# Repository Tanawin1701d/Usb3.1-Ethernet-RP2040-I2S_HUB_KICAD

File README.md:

# Usb3.1-Ethernet-RP2040-I2S_HUB_KICAD

- This project relies on Kicad 9.0

## features

### input
- usb 3.1 gen2
### output
- usb 3.0 (2 ports)
- ethernet (1 rj45 port)
- microphone + speaker (stero 3mm jack)
### processor & ic
- Rasberry pi (RP2040)
- tmp235 (temperature sensor)
- tusb8041 (usb hub)
- RTL8153B-VB (ethernet)

### repo structure

```
F---- doc (document for each ICs)
F---- finalProj
           |F---- hub (kicad file)
F---- symFoot (footprint for each ICs)
D---- bom.xlsx (bill of material for all components except pcb board)
```

## preview

### schematic

### layout

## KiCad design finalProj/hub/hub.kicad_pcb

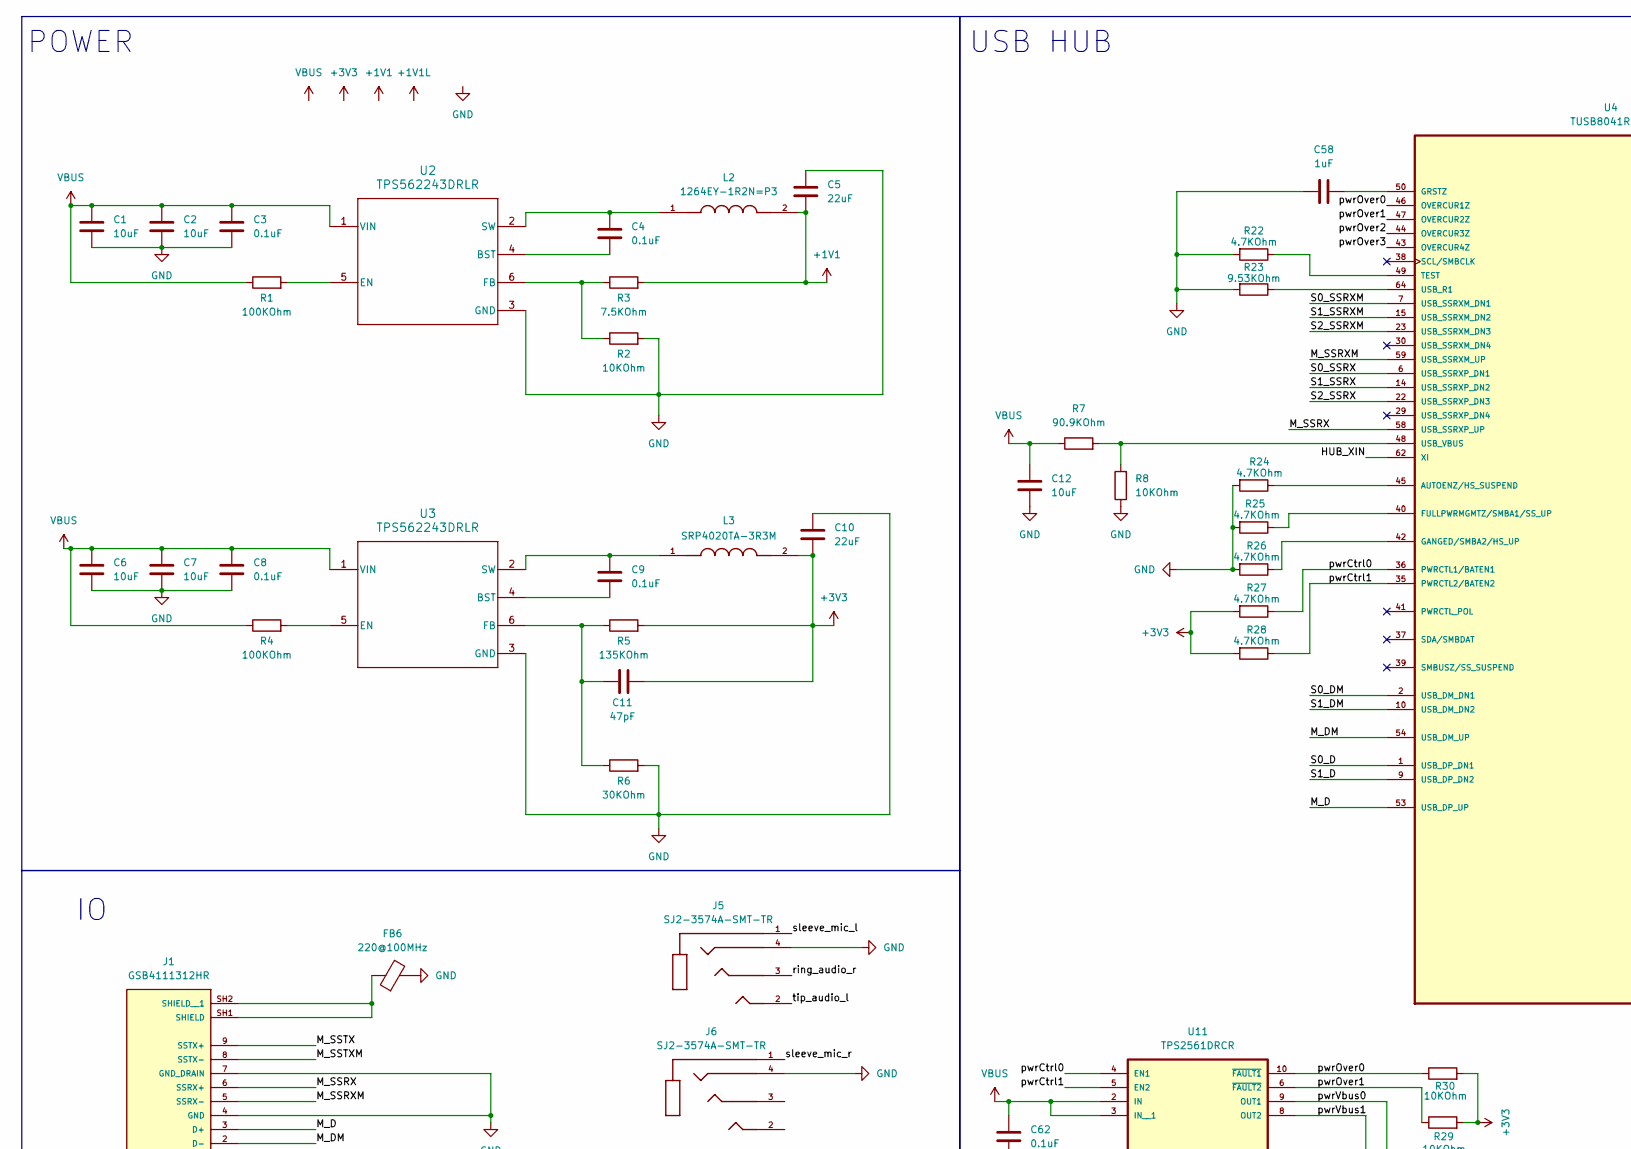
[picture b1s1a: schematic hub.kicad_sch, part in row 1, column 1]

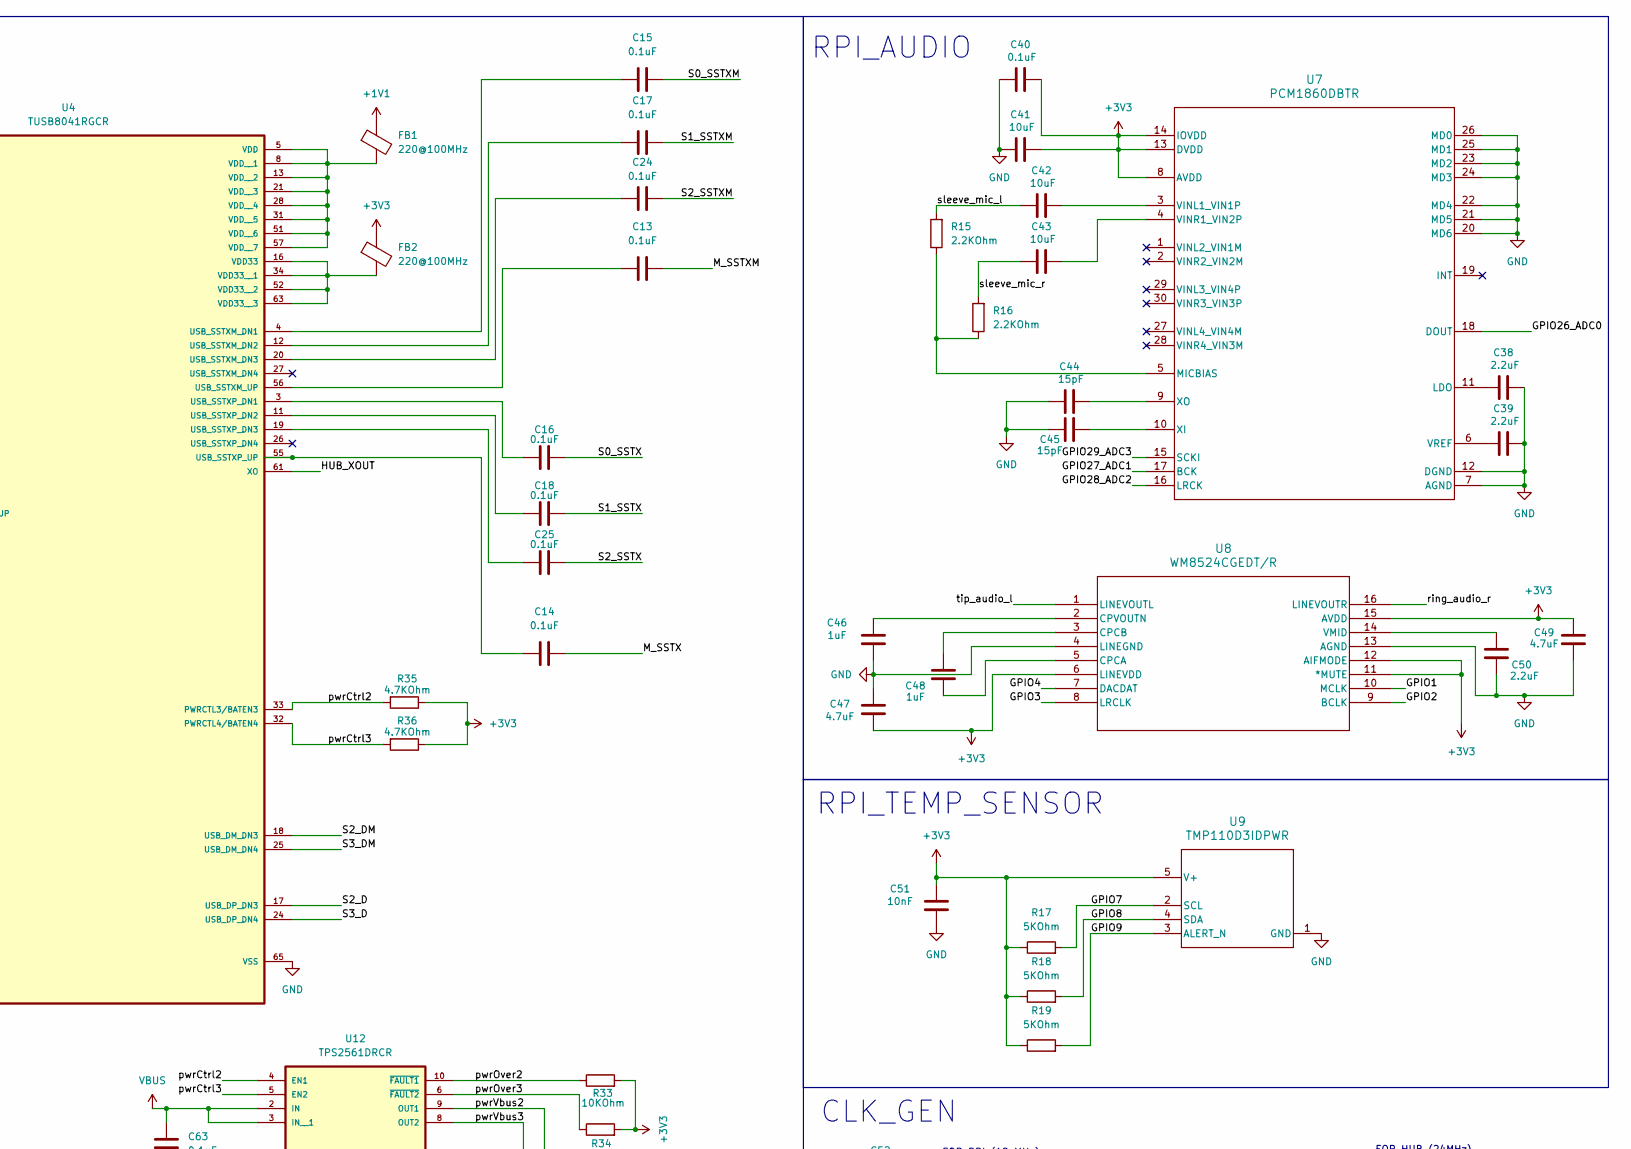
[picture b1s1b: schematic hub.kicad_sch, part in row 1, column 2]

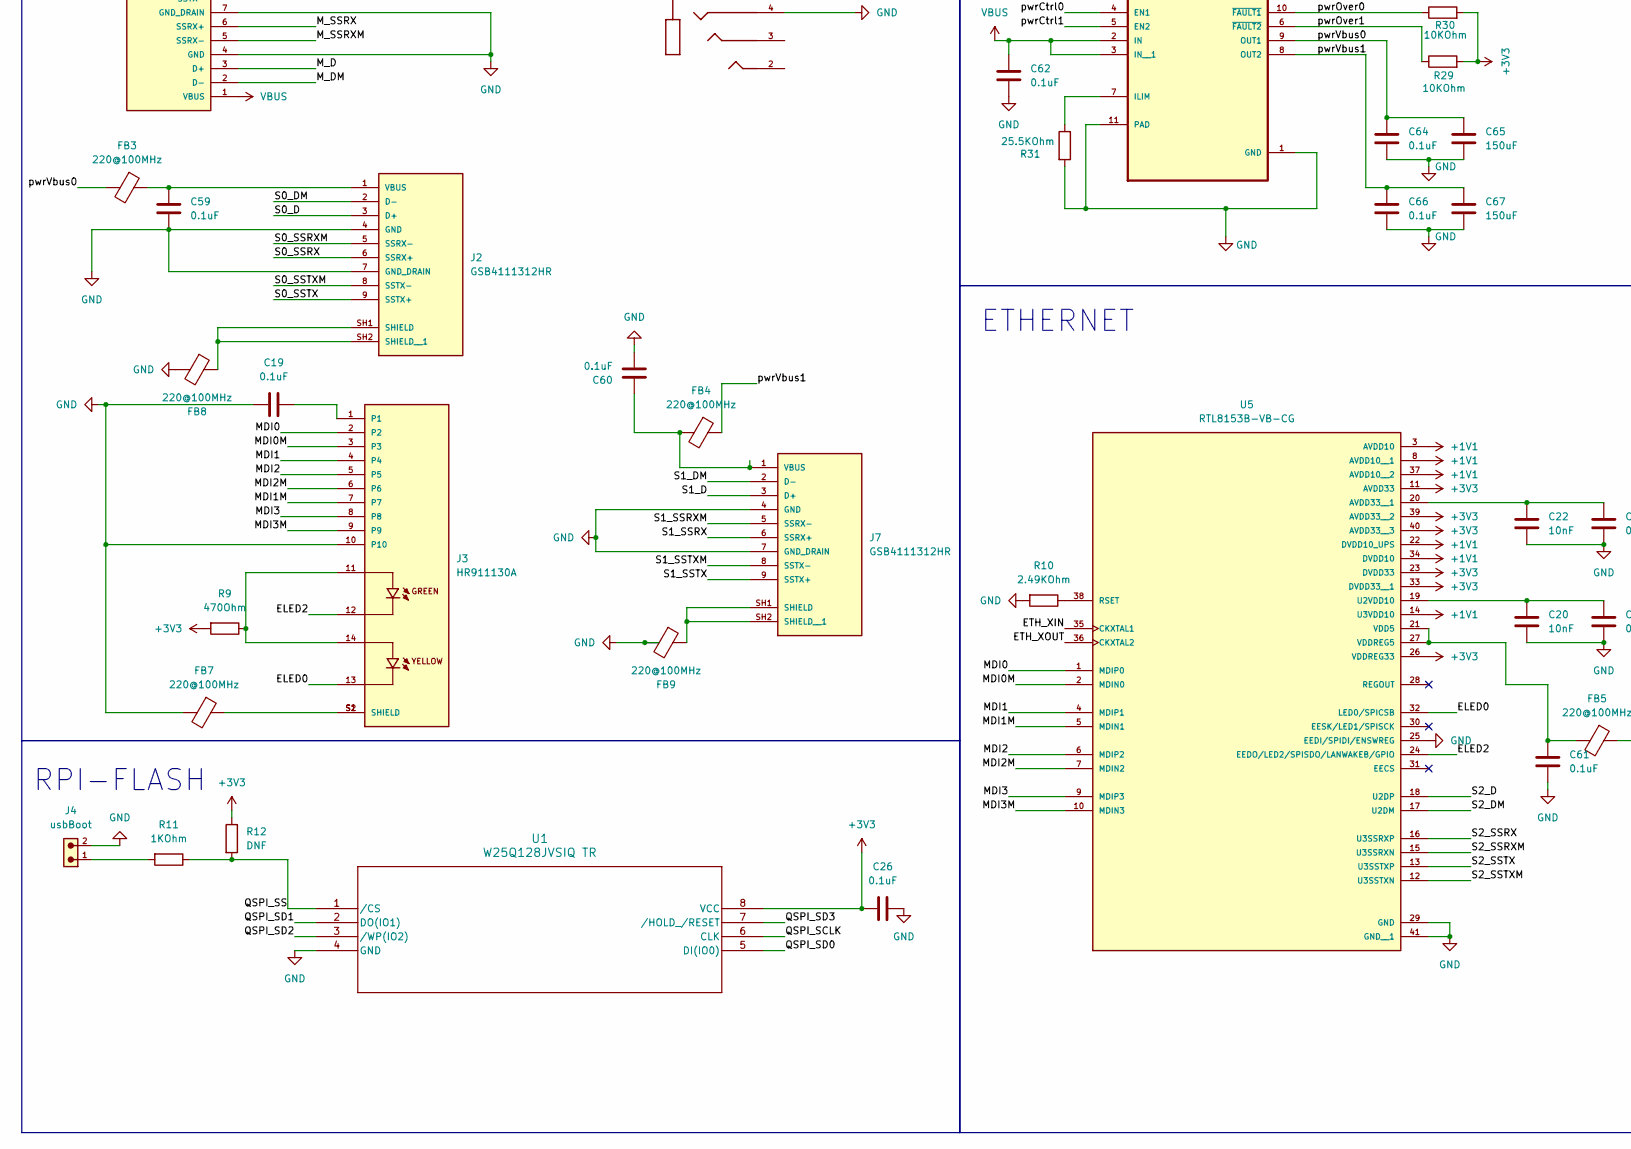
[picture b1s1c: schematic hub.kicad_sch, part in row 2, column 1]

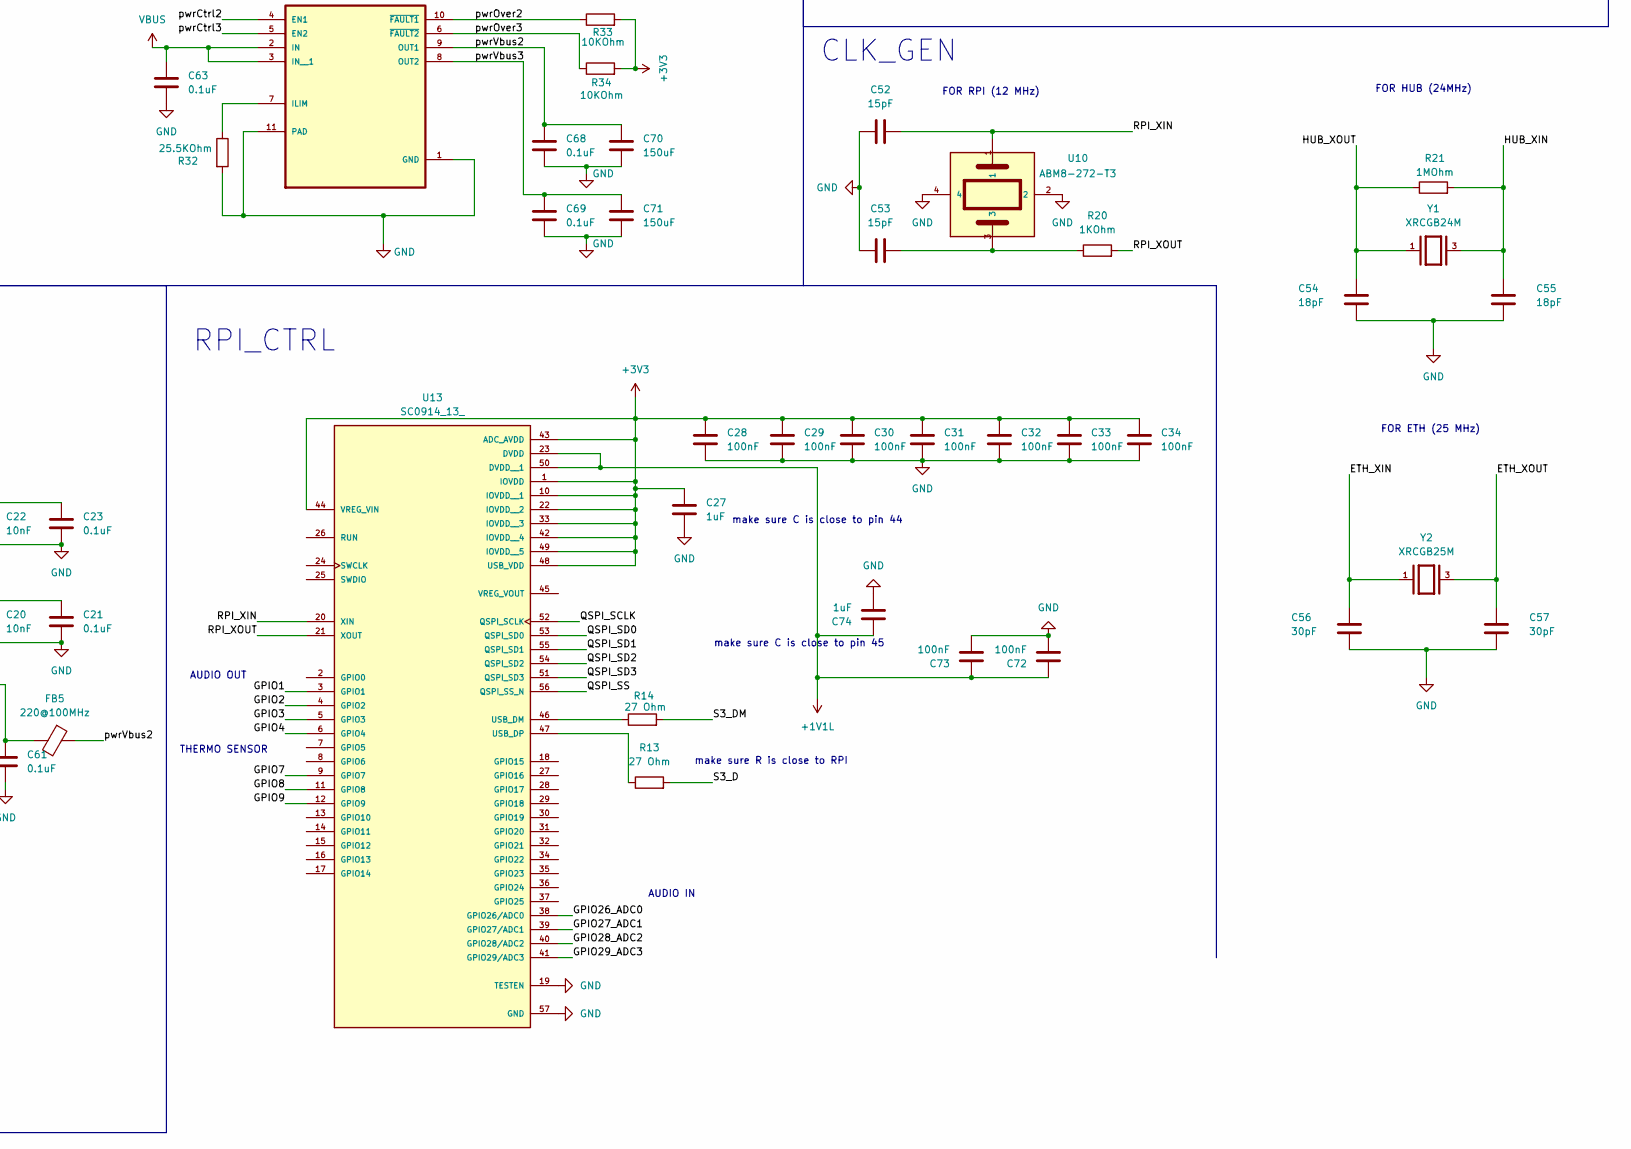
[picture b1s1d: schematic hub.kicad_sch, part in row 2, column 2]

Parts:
C1, C2, C6, C7, C12, C41, C42, C43: 10uF; C_0805_2012Metric_Pad1.18x1.45mm_HandSolder
C3, C4, C8, C9, C13, C14, C15, C16, C17, C18, C19, C21, C23, C24, C25, C26, C40, C59, C60, C61, C62, C63, C64, C66, C68, C69: 0.1uF; C_0603_1608Metric_Pad1.08x0.95mm_HandSolder
C5, C10: 22uF; C_1206_3216Metric_Pad1.33x1.80mm_HandSolder
C11: 47pF; C_0603_1608Metric_Pad1.08x0.95mm_HandSolder
C20, C22, C51: 10nF; C_0603_1608Metric_Pad1.08x0.95mm_HandSolder
C27, C46, C48, C58, C74: 1uF; C_0603_1608Metric_Pad1.08x0.95mm_HandSolder
C28, C29, C30, C31, C32, C33, C34, C72, C73: 100nF; C_0603_1608Metric_Pad1.08x0.95mm_HandSolder
C38, C39, C50: 2.2uF; C_0603_1608Metric_Pad1.08x0.95mm_HandSolder
C44, C45, C52, C53: 15pF; C_0805_2012Metric_Pad1.18x1.45mm_HandSolder
C47, C49: 4.7uF; C_0805_2012Metric_Pad1.18x1.45mm_HandSolder
C54, C55: 18pF; C_0603_1608Metric_Pad1.08x0.95mm_HandSolder
C56, C57: 30pF; C_0805_2012Metric_Pad1.18x1.45mm_HandSolder
C65, C67, C70, C71: 150uF; CP_Radial_D6.3mm_P2.50mm
FB1, FB2, FB3, FB4, FB5, FB6, FB7, FB8, FB9: 220@100MHz; L_0603_1608Metric_Pad1.05x0.95mm_HandSolder
J1, J2, J7: GSB4111312HR; AMPHENOL_GSB4111312HR; PARTREV B
J3: HR911130A; HANRUN_HR911130A; PARTREV A
J4: usbBoot; 61300211121
J5, J6: SJ2-3574A-SMT-TR; SAMESKY_SJ2-3574A-SMT-TR; PARTREV 1.05
L2: 1264EY-1R2N=P3; IND_1264EY-1R2N=P3; PARTREV N/A
L3: SRP4020TA-3R3M; IND_SRP4020TA-3R3M
R1, R4: 100KOhm; R_0603_1608Metric_Pad0.98x0.95mm_HandSolder
R2, R8, R29, R30, R33, R34: 10KOhm; R_0603_1608Metric_Pad0.98x0.95mm_HandSolder
R3: 7.5KOhm; R_0603_1608Metric_Pad0.98x0.95mm_HandSolder
R5: 135KOhm; R_0603_1608Metric_Pad0.98x0.95mm_HandSolder
R6: 30KOhm; R_0603_1608Metric_Pad0.98x0.95mm_HandSolder
R7: 90.9KOhm; R_0603_1608Metric_Pad0.98x0.95mm_HandSolder
R9: 470Ohm; R_0603_1608Metric_Pad0.98x0.95mm_HandSolder
R10: 2.49KOhm; R_0603_1608Metric_Pad0.98x0.95mm_HandSolder
R11, R20: 1KOhm; R_0603_1608Metric_Pad0.98x0.95mm_HandSolder
R12: DNF; R_0603_1608Metric_Pad0.98x0.95mm_HandSolder
R13, R14: 27 Ohm; R_0603_1608Metric_Pad0.98x0.95mm_HandSolder
R15, R16: 2.2KOhm; R_0603_1608Metric_Pad0.98x0.95mm_HandSolder
R17, R18, R19: 5KOhm; R_0603_1608Metric_Pad0.98x0.95mm_HandSolder
R21: 1MOhm; R_0603_1608Metric_Pad0.98x0.95mm_HandSolder
R22, R24, R25, R26, R27, R28, R35, R36: 4.7KOhm; R_0603_1608Metric_Pad0.98x0.95mm_HandSolder
R23: 9.53KOhm; R_0603_1608Metric_Pad0.98x0.95mm_HandSolder
R31, R32: 25.5KOhm; R_0603_1608Metric_Pad0.98x0.95mm_HandSolder
U1: W25Q128JVSIQ TR; SOIC_208MIL_WIN
U2, U3: TPS562243DRLR; DRL0006A-MFG
U4: TUSB8041RGCR; QFN50P900X900X100-65N
U5: RTL8153B-VB-CG; QFN40P500X500X90-41N; PARTREV 1.4
U7: PCM1860DBTR; DBT0030A_N
U8: WM8524CGEDT/R; TSSOP16_DM013.B_CIR
U9: TMP110D3IDPWR; DPW0005A-MFG
U10: ABM8-272-T3
U11, U12: TPS2561DRCR; VREG_V62_16624-01YE
U13: SC0914_13_; QFN40P700X700X90-57N; PARTREV 2.2
Y1: XRCGB24M; OSC_XRCGB24M000F2P00R0; PARTREV N/A
Y2: XRCGB25M; OSC_XRCGB25M000F3M00R0; PARTREV N/A

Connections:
+1V1: C5.1, FB1.1, L2.2, R3.2, U5.3 (AVDD10), U5.8 (AVDD10__1), U5.14 (U3VDD10), U5.22 (DVDD10_UPS), U5.34 (DVDD10), U5.37 (AVDD10__2)
+3V3: C10.1, C11.1, C26.1, C27.1, C28.1, C29.1, C30.1, C31.1, C32.1, C33.1, C34.1, C40.2, C41.2, C47.1, C49.2, C51.2, FB2.1, L3.2, R5.2, R9.2, R12.1, R17.1, R18.1, R19.1, R27.2, R28.2, R29.2, R30.2, R33.2, R34.2, R35.1, R36.1, U1.8 (VCC), U5.11 (AVDD33), U5.23 (DVDD33), U5.26 (VDDREG33), U5.33 (DVDD33__1), U5.39 (AVDD33__2), U5.40 (AVDD33__3), U7.8 (AVDD), U7.13 (DVDD), U7.14 (IOVDD), U8.6 (LINEVDD), U8.11 (*MUTE), U8.12 (AIFMODE), U8.15 (AVDD), U9.5 (V+), U13.1 (IOVDD), U13.10 (IOVDD__1), U13.22 (IOVDD__2), U13.33 (IOVDD__3), U13.42 (IOVDD__4), U13.43 (ADC_AVDD), U13.44 (VREG_VIN), U13.48 (USB_VDD), U13.49 (IOVDD__5)
/ELED0: J3.13, U5.32 (LED0/SPICSB)
/ELED2: J3.12, U5.24 (EEDO/LED2/SPISDO/LANWAKEB/GPIO)
/ETH_XIN: C56.1, U5.35 (CKXTAL1), Y2.1
/ETH_XOUT: C57.1, U5.36 (CKXTAL2), Y2.3
/GPIO1: U8.10 (MCLK), U13.3 (GPIO1)
/GPIO2: U8.9 (BCLK), U13.4 (GPIO2)
/GPIO3: U8.8 (LRCLK), U13.5 (GPIO3)
/GPIO4: U8.7 (DACDAT), U13.6 (GPIO4)
/GPIO7: R17.2, U9.2 (SCL), U13.9 (GPIO7)
/GPIO8: R18.2, U9.4 (SDA), U13.11 (GPIO8)
/GPIO9: R19.2, U9.3 (ALERT_N), U13.12 (GPIO9)
/GPIO26_ADC0: U7.18 (DOUT), U13.38 (GPIO26/ADC0)
/GPIO27_ADC1: U7.17 (BCK), U13.39 (GPIO27/ADC1)
/GPIO28_ADC2: U7.16 (LRCK), U13.40 (GPIO28/ADC2)
/GPIO29_ADC3: U7.15 (SCKI), U13.41 (GPIO29/ADC3)
/HUB_XIN: C55.1, R21.2, U4.62 (XI), Y1.3
/HUB_XOUT: C54.1, R21.1, U4.61 (XO), Y1.1
/MDI0: J3.2, U5.1 (MDIP0)
/MDI0M: J3.3, U5.2 (MDIN0)
/MDI1: J3.4, U5.4 (MDIP1)
/MDI1M: J3.7, U5.5 (MDIN1)
/MDI2: J3.5, U5.6 (MDIP2)
/MDI2M: J3.6, U5.7 (MDIN2)
/MDI3: J3.8, U5.9 (MDIP3)
/MDI3M: J3.9, U5.10 (MDIN3)
/M_D: J1.3 (D+), U4.53 (USB_DP_UP)
/M_DM: J1.2 (D-), U4.54 (USB_DM_UP)
/M_SSRX: J1.6 (SSRX+), U4.58 (USB_SSRXP_UP)
/M_SSRXM: J1.5 (SSRX-), U4.59 (USB_SSRXM_UP)
/M_SSTX: C14.2, J1.9 (SSTX+)
/M_SSTXM: C13.2, J1.8 (SSTX-)
/QSPI_SCLK: U1.6 (CLK), U13.52 (QSPI_SCLK)
/QSPI_SD0: U1.5 (DI(IO0)), U13.53 (QSPI_SD0)
/QSPI_SD1: U1.2 (DO(IO1)), U13.55 (QSPI_SD1)
/QSPI_SD2: U1.3 (/WP(IO2)), U13.54 (QSPI_SD2)
/QSPI_SD3: U1.7 (/HOLD_/RESET), U13.51 (QSPI_SD3)
/QSPI_SS: R11.1, R12.2, U1.1 (/CS), U13.56 (QSPI_SS_N)
/RPI_XIN: C52.1, U10.1, U13.20 (XIN)
/RPI_XOUT: R20.2, U13.21 (XOUT)
/S0_D: J2.3 (D+), U4.1 (USB_DP_DN1)
/S0_DM: J2.2 (D-), U4.2 (USB_DM_DN1)
/S0_SSRX: J2.6 (SSRX+), U4.6 (USB_SSRXP_DN1)
/S0_SSRXM: J2.5 (SSRX-), U4.7 (USB_SSRXM_DN1)
/S0_SSTX: C16.2, J2.9 (SSTX+)
/S0_SSTXM: C15.2, J2.8 (SSTX-)
/S1_D: J7.3 (D+), U4.9 (USB_DP_DN2)
/S1_DM: J7.2 (D-), U4.10 (USB_DM_DN2)
/S1_SSRX: J7.6 (SSRX+), U4.14 (USB_SSRXP_DN2)
/S1_SSRXM: J7.5 (SSRX-), U4.15 (USB_SSRXM_DN2)
/S1_SSTX: C18.2, J7.9 (SSTX+)
/S1_SSTXM: C17.2, J7.8 (SSTX-)
/S2_D: U4.17 (USB_DP_DN3), U5.18 (U2DP)
/S2_DM: U4.18 (USB_DM_DN3), U5.17 (U2DM)
/S2_SSRX: U4.22 (USB_SSRXP_DN3), U5.16 (U3SSRXP)
/S2_SSRXM: U4.23 (USB_SSRXM_DN3), U5.15 (U3SSRXN)
/S2_SSTX: C25.2, U5.13 (U3SSTXP)
/S2_SSTXM: C24.2, U5.12 (U3SSTXN)
/S3_D: R13.2, U4.24 (USB_DP_DN4)
/S3_DM: R14.2, U4.25 (USB_DM_DN4)
/pwrCtrl0: R27.1, U4.36 (PWRCTL1/BATEN1), U11.4 (EN1)
/pwrCtrl1: R28.1, U4.35 (PWRCTL2/BATEN2), U11.5 (EN2)
/pwrCtrl2: R35.2, U4.33 (PWRCTL3/BATEN3), U12.4 (EN1)
/pwrCtrl3: R36.2, U4.32 (PWRCTL4/BATEN4), U12.5 (EN2)
/pwrOver0: R30.1, U4.46 (OVERCUR1Z), U11.10 (~FAULT1)
/pwrOver1: R29.1, U4.47 (OVERCUR2Z), U11.6 (~FAULT2)
/pwrOver2: R33.1, U4.44 (OVERCUR3Z), U12.10 (~FAULT1)
/pwrOver3: R34.1, U4.43 (OVERCUR4Z), U12.6 (~FAULT2)
/pwrVbus0: C64.2, C65.2, FB3.2, U11.9 (OUT1)
/pwrVbus1: C66.2, C67.2, FB4.1, U11.8 (OUT2)
/pwrVbus2: C68.2, C70.2, FB5.1, U12.9 (OUT1)
/pwrVbus3: C69.2, C71.2, U12.8 (OUT2)
/ring_audio_r: J5.3, U8.16 (LINEVOUTR)
/sleeve_mic_l: C42.1, J5.1, R15.2
/sleeve_mic_r: C43.1, J6.1, R16.2
/tip_audio_l: J5.2, U8.1 (LINEVOUTL)
GND: C1.1, C2.1, C3.1, C5.2, C6.1, C7.1, C8.1, C10.2, C12.1, C19.1, C20.2, C21.2, C22.2, C23.2, C26.2, C27.2, C28.2, C29.2, C30.2, C31.2, C32.2, C33.2, C34.2, C38.2, C39.2, C40.1, C41.1, C44.1, C45.1, C46.1, C47.2, C49.1, C50.1, C51.1, C52.2, C53.2, C54.2, C55.2, C56.2, C57.2, C58.2, C59.1, C60.1, C61.1, C62.1, C63.1, C64.1, C65.1, C66.1, C67.1, C68.1, C69.1, C70.1, C71.1, C72.2, C73.2, C74.2, FB6.2, FB7.2, FB8.2, FB9.2, J1.4 (GND), J1.7 (GND_DRAIN), J2.4 (GND), J2.7 (GND_DRAIN), J3.10, J4.2, J5.4, J6.4, J7.4 (GND), J7.7 (GND_DRAIN), R2.2, R6.2, R8.1, R10.2, R22.2, R23.2, R24.2, R25.2, R26.2, R31.2, R32.2, U1.4 (GND), U2.3 (GND), U3.3 (GND), U4.65 (VSS), U5.25 (EEDI/SPIDI/ENSWREG), U5.29 (GND), U5.41 (GND__1), U7.7 (AGND), U7.12 (DGND), U7.20 (MD6), U7.21 (MD5), U7.22 (MD4), U7.23 (MD2), U7.24 (MD3), U7.25 (MD1), U7.26 (MD0), U8.4 (LINEGND), U8.13 (AGND), U9.1 (GND), U10.2, U10.4, U11.1 (GND), U11.11 (PAD), U12.1 (GND), U12.11 (PAD), U13.19 (TESTEN), U13.57 (GND)
unnamed: C53.1, R20.1, U10.3
unnamed: C72.1, C73.1, C74.1, U13.23 (DVDD), U13.50 (DVDD__1)
unnamed: FB7.1, J3.S1 (SHIELD), J3.S2 (SHIELD)
unnamed: FB6.1, J1.SH1 (SHIELD), J1.SH2 (SHIELD__1)
unnamed: FB8.1, J2.SH1 (SHIELD), J2.SH2 (SHIELD__1)
unnamed: C59.2, FB3.1, J2.1 (VBUS)
unnamed: C19.2, J3.1
unnamed: J3.11, J3.14, R9.1
unnamed: J4.1, R11.2
unnamed: FB9.1, J7.SH1 (SHIELD), J7.SH2 (SHIELD__1)
unnamed: C60.2, FB4.2, J7.1 (VBUS)
unnamed: C4.1, U2.4 (BST)
unnamed: R1.2, U2.5 (EN)
unnamed: R2.1, R3.1, U2.6 (FB)
unnamed: C4.2, L2.1, U2.2 (SW)
unnamed: C9.1, U3.4 (BST)
unnamed: R4.2, U3.5 (EN)
unnamed: C11.2, R5.1, R6.1, U3.6 (FB)
unnamed: C9.2, L3.1, U3.2 (SW)
unnamed: R24.1, U4.45 (AUTOENZ/HS_SUSPEND)
unnamed: R25.1, U4.40 (FULLPWRMGMTZ/SMBA1/SS_UP)
unnamed: R26.1, U4.42 (GANGED/SMBA2/HS_UP)
unnamed: C58.1, U4.50 (GRSTZ)
unnamed: R22.1, U4.49 (TEST)
unnamed: R23.1, U4.64 (USB_R1)
unnamed: C15.1, U4.4 (USB_SSTXM_DN1)
unnamed: C17.1, U4.12 (USB_SSTXM_DN2)
unnamed: C24.1, U4.20 (USB_SSTXM_DN3)
unnamed: C13.1, U4.56 (USB_SSTXM_UP)
unnamed: C16.1, U4.3 (USB_SSTXP_DN1)
unnamed: C18.1, U4.11 (USB_SSTXP_DN2)
unnamed: C25.1, U4.19 (USB_SSTXP_DN3)
unnamed: C14.1, U4.55 (USB_SSTXP_UP)
unnamed: R7.2, R8.2, U4.48 (USB_VBUS)
unnamed: FB2.2, U4.16 (VDD33), U4.34 (VDD33__1), U4.52 (VDD33__2), U4.63 (VDD33__3)
unnamed: FB1.2, U4.5 (VDD), U4.8 (VDD__1), U4.13 (VDD__2), U4.21 (VDD__3), U4.28 (VDD__4), U4.31 (VDD__5), U4.51 (VDD__6), U4.57 (VDD__7)
unnamed: C22.1, C23.1, U5.20 (AVDD33__1)
unnamed: R10.1, U5.38 (RSET)
unnamed: C20.1, C21.1, U5.19 (U2VDD10)
unnamed: C61.2, FB5.2, U5.21 (VDD5), U5.27 (VDDREG5)
unnamed: C38.1, U7.11 (LDO)
unnamed: R15.1, R16.1, U7.5 (MICBIAS)
unnamed: C42.2, U7.3 (VINL1_VIN1P)
unnamed: C43.2, U7.4 (VINR1_VIN2P)
unnamed: C39.1, U7.6 (VREF)
unnamed: C45.2, U7.10 (XI)
unnamed: C44.2, U7.9 (XO)
unnamed: C48.1, U8.5 (CPCA)
unnamed: C48.2, U8.3 (CPCB)
unnamed: C46.2, U8.2 (CPVOUTN)
unnamed: C50.2, U8.14 (VMID)
unnamed: R31.1, U11.7 (ILIM)
unnamed: R32.1, U12.7 (ILIM)
unnamed: R14.1, U13.46 (USB_DM)
unnamed: R13.1, U13.47 (USB_DP)
VBUS: C1.2, C2.2, C3.2, C6.2, C7.2, C8.2, C12.2, C62.2, C63.2, J1.1 (VBUS), R1.1, R4.1, R7.1, U2.1 (VIN), U3.1 (VIN), U11.2 (IN), U11.3 (IN__1), U12.2 (IN), U12.3 (IN__1)

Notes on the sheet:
FOR RPI (12 MHz)
RPI_AUDIO
CLK_GEN
make sure R is close to RPI
AUDIO OUT
RPI_TEMP_SENSOR
RPI_CTRL
RPI-FLASH
USB HUB
make sure C is close to pin 45
make sure C is close to pin 44
FOR ETH (25 MHz)
AUDIO IN
ETHERNET
FOR HUB (24MHz)
THERMO SENSOR
POWER

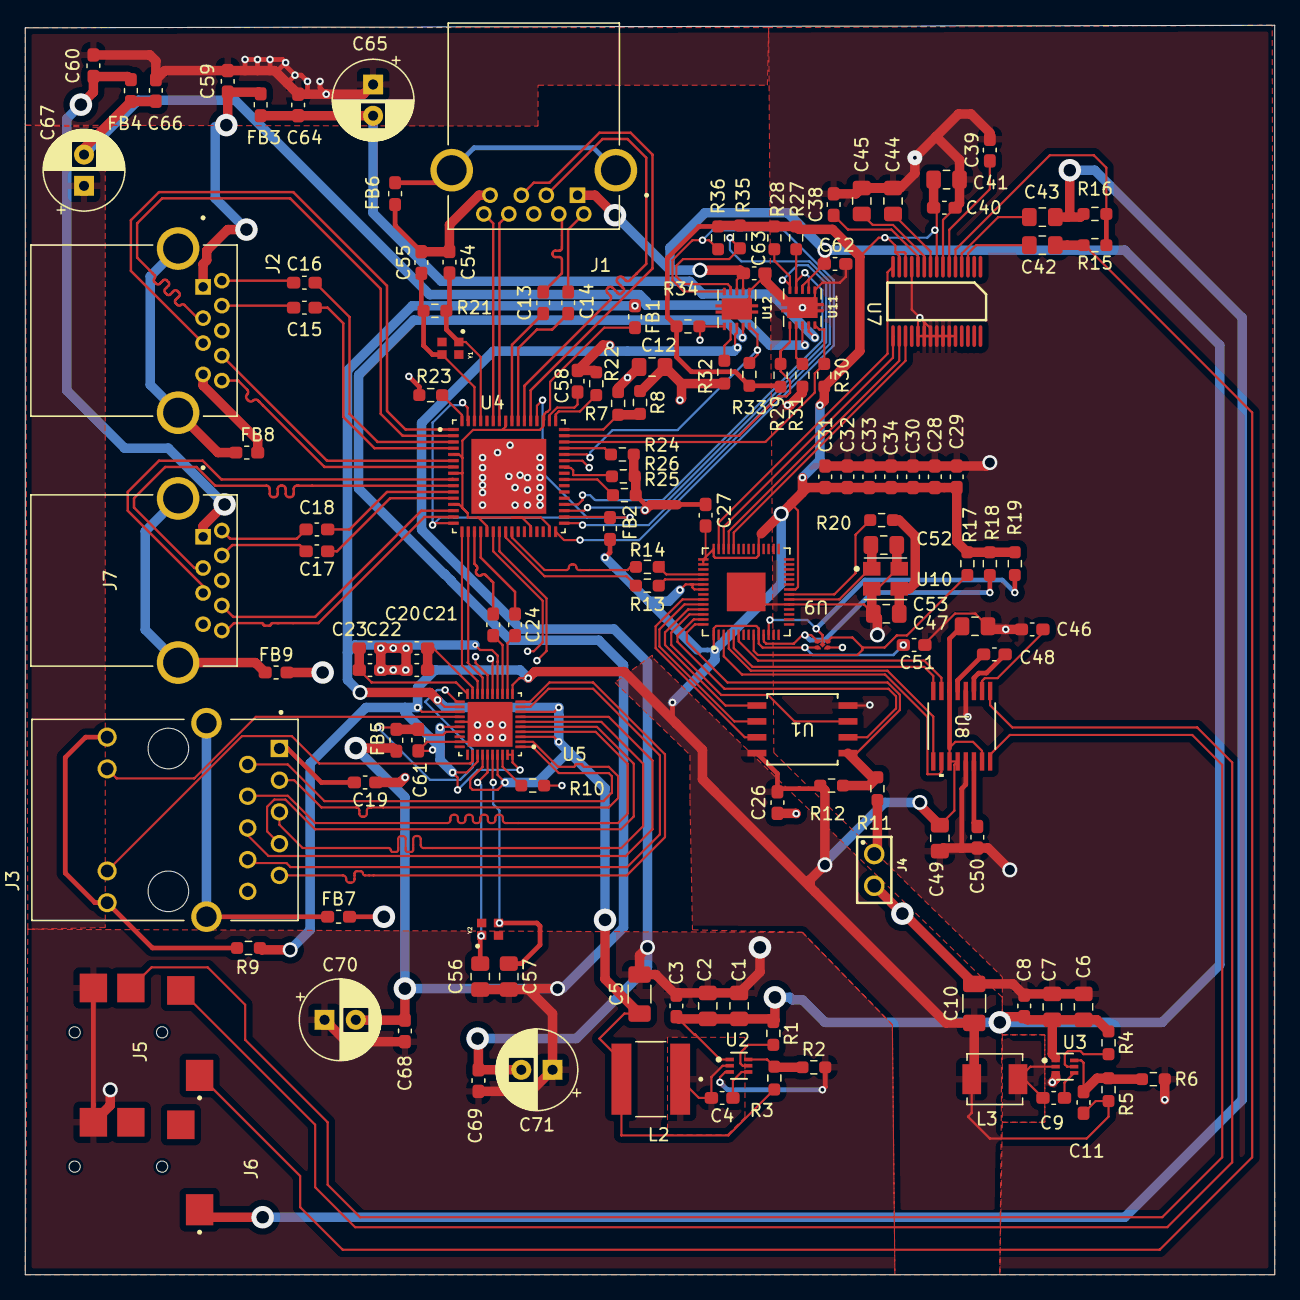
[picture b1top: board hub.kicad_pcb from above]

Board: 4 copper layers, 100.0 x 100.0 mm, 136 parts (0 on the bottom side), 133 nets.

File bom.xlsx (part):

Reference | Footprint | voltage rating | tol | temp coff | price |  |  |  | Value | Datasheet | DNP | Exclude from BOM | Exclude from Board | source
C1,C2,C6,C7,C12,C41,C42,C43 | Capacitor_SMD:C_0805_2012Metric_Pad1.18x1.45mm_HandSolder | 10.0 | +-10 | x7r | 0.38 |  | 8 | 3.04 | 10uF | ~ |  |  |  | https://www.digikey.co.th/en/products/detail/samsung-electro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
C3,C4,C8,C9,C13,C14,C15,C16,C17,C18,C19,C21,C23,C24,C25,C26,C40,C59,C60,C61,C62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 | Capacitor_SMD:C_0603_1608Metric_Pad1.08x0.95mm_HandSolder | 25.0 | +-10 | x7r | 0.01500 |  | 26 | 0.39 | 0.1uF | ~ |  |  |  | https://www.digikey.co.th/en/products/detail/samsung-electro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
C5,C10 | Capacitor_SMD:C_1206_3216Metric_Pad1.33x1.80mm_HandSolder | 10.0 | +-20 | x7r | 0.20300 |  | 2 | 0.406 | 22uF | ~ |  |  |  | https://www.digikey.co.th/en/products/detail/samsung-electro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
C11 | Capacitor_SMD:C_0603_1608Metric_Pad1.08x0.95mm_HandSolder | 50.0 | +-10 | x7r | 0.10200 |  | 1 | 0.102 | 47pF | ~ |  |  |  | https://www.digikey.co.th/en/products/detail/kyocera-avx/060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
C20,C22,C51 | Capacitor_SMD:C_0603_1608Metric_Pad1.08x0.95mm_HandSolder | 50.0 | +-10 | x7r | 0.00900 |  | 3 | 0.027 | 10nF | ~ |  |  |  | https://www.digikey.co.th/en/products/detail/samsung-electro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
C27,C46,C48,C58,C74 | Capacitor_SMD:C_0603_1608Metric_Pad1.08x0.95mm_HandSolder | 10.0 | +-10 | x7r | 0.00600 |  | 5 | 0.03 | 1uF | ~ |  |  |  | https://www.digikey.co.th/en/products/detail/samsung-electro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
C28,C29,C30,C31,C32,C33,C34,C72,C73 | Capacitor_SMD:C_0603_1608Metric_Pad1.08x0.95mm_HandSolder | 25.0 | +-10 | x7r | 0.01500 |  | 9 | 0.135 | 0.1uF | ~ |  |  |  | https://www.digikey.co.th/en/products/detail/samsung-electro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
C38,C39,C50 | Capacitor_SMD:C_0603_1608Metric_Pad1.08x0.95mm_HandSolder | 10.0 | +-10 | x7r | 0.02100 |  | 3 | 0.063 | 2.2uF | ~ |  |  |  | https://www.digikey.co.th/en/products/detail/samsung-electro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
C44,C45,C52,C53 | Capacitor_SMD:C_0805_2012Metric_Pad1.18x1.45mm_HandSolder | 50.0 | +-10 | x7r | 0.10600 |  | 4 | 0.424 | 15pF | ~ |  |  |  | https://www.digikey.co.th/en/products/detail/kyocera-avx/080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
C47,C49 | Capacitor_SMD:C_0805_2012Metric_Pad1.18x1.45mm_HandSolder | 16.0 | +-10 | x7r | 0.10800 |  | 2 | 0.216 | 4.7uF | ~ |  |  |  | https://www.digikey.co.th/en/products/detail/samsung-electro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
C54,C55 | Capacitor_SMD:C_0603_1608Metric_Pad1.08x0.95mm_HandSolder | 50.0 | +-10 | x7r | 0.12900 |  | 2 | 0.258 | 18pF | ~ |  |  |  | https://www.digikey.co.th/en/products/detail/kemet/C0603C180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
C56,C57 | 0805 (2012 Metric) | 50.0 | +-10 | x7r | 0.17300 |  | 2 | 0.346 | 30pF | ~ |  |  |  | https://www.digikey.co.th/en/products/detail/kemet/C0805C300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
C65,C67,C70,C71 | custom (polar ) | 6.3 | +-20 | x7r | 0.22400 |  | 4 | 0.896 | 150uF | ~ |  |  |  | https://www.digikey.co.th/en/products/detail/rubycon/25ZLJ15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
FB1,FB2,FB3,FB4,FB5,FB6,FB7,FB8,FB9 | 603.0 |  |  |  | 0.057 |  | 9.0 | 0.513 | 220@100MHz | ~ |  |  |  | https://www.digikey.co.th/en/products/detail/tdk-corporation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
J1 | GSB4111312HR:AMPHENOL_GSB4111312HR |  |  |  | 0.92 |  | 3.0 | 2.76 | GSB4111312HR |  |  |  |  | https://www.digikey.co.th/en/products/detail/amphenol-cs-com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
J3 | HR911130A:HANRUN_HR911130A |  |  |  | 1.14302 |  | 1.0 | 1.14302 | HR911130A |  |  |  |  | https://www.chipspulse.com/product/Hanrun/HR911130A.html?utm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
J4 | pin01x02:61300211121 |  |  |  | 0.113 |  | 1.0 | 0.113 | usbBoot |  |  |  |  | https://th.mouser.com/ProductDetail/Wurth-Elektronik/6130021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
J5,J6 | SJ2_3574A_SMT_TR:SAMESKY_SJ2-3574A-SMT-TR |  |  |  | 0.87 |  | 2.0 | 1.74 | SJ2-3574A-SMT-TR |  |  |  |  | https://www.digikey.co.th/en/products/detail/same-sky-former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
L1 | custom |  |  |  | 0.328 |  | 1.0 | 0.328 | 1.2uH | ~ |  |  |  | https://www.digikey.co.th/en/products/detail/murata-electron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
L2 | custom |  |  |  | 0.838 |  | 1.0 | 0.838 | 3.3uH(SRP4020TA_3R3M) | ~ |  |  |  | https://www.digikey.co.th/en/products/detail/bourns-inc/SRP4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
R1,R4 | Resistor_SMD:R_0603_1608Metric_Pad0.98x0.95mm_HandSolder |  |  |  | 0.027 |  | 2.0 | 0.054 | 100KOhm | ~ |  |  |  | https://www.digikey.co.th/en/products/detail/susumu/RR0816P-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
R2,R8,R29,R30,R33,R34 | Resistor_SMD:R_0603_1608Metric_Pad0.98x0.95mm_HandSolder |  |  |  | 0.033 |  | 6.0 | 0.198 | 10KOhm | ~ |  |  |  | https://www.digikey.co.th/en/products/detail/panasonic-elect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
R3 | Resistor_SMD:R_0603_1608Metric_Pad0.98x0.95mm_HandSolder |  |  |  | 0.009 |  | 1.0 | 0.009 | 7.5KOhm | ~ |  |  |  | https://www.digikey.co.th/en/products/detail/yageo/RC0603FR-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
R5 | Resistor_SMD:R_0603_1608Metric_Pad0.98x0.95mm_HandSolder |  |  |  | 0.101 |  | 1.0 | 0.101 | 135KOhm | ~ |  |  |  | https://www.digikey.co.th/en/products/detail/yageo/RT0603BRD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
R6 | Resistor_SMD:R_0603_1608Metric_Pad0.98x0.95mm_HandSolder |  |  |  | 0.008 |  | 1.0 | 0.008 | 30KOhm | ~ |  |  |  | https://www.digikey.co.th/en/products/detail/yageo/RC0603JR-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
R7 | Resistor_SMD:R_0603_1608Metric_Pad0.98x0.95mm_HandSolder |  |  |  | 0.009 |  | 1.0 | 0.009 | 90.9KOhm | ~ |  |  |  | https://www.digikey.co.th/en/products/detail/yageo/RC0603FR-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
R9 | Resistor_SMD:R_0603_1608Metric_Pad0.98x0.95mm_HandSolder |  |  |  | 0.008 |  | 1.0 | 0.008 | 470Ohm | ~ |  |  |  | https://www.digikey.co.th/en/products/detail/yageo/RC0603JR-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
R10 | Resistor_SMD:R_0603_1608Metric_Pad0.98x0.95mm_HandSolder |  |  |  | 0.03 |  | 1.0 | 0.03 | 2.49KOhm | ~ |  |  |  | https://www.digikey.co.th/en/products/detail/vishay-dale/CRC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
R11,R20 | Resistor_SMD:R_0603_1608Metric_Pad0.98x0.95mm_HandSolder |  |  |  | 0.02 |  | 2.0 | 0.04 | 1KOhm | ~ |  |  |  | https://www.digikey.co.th/en/products/detail/stackpole-elect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
R12 | Resistor_SMD:R_0603_1608Metric_Pad0.98x0.95mm_HandSolder |  |  |  |  |  |  | 0 | DNF | ~
R13,R14 | Resistor_SMD:R_0603_1608Metric_Pad0.98x0.95mm_HandSolder |  |  |  | 0.008 |  | 2.0 | 0.016 | 27 Ohm | ~ |  |  |  | https://www.digikey.co.th/en/products/detail/yageo/RC0603JR-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
R15,R16 | Resistor_SMD:R_0603_1608Metric_Pad0.98x0.95mm_HandSolder |  |  |  | 0.028 |  | 2.0 | 0.056 | 2.2KOhm | ~ |  |  |  | https://www.digikey.co.th/en/products/detail/te-connectivity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
R17,R18,R19 | Resistor_SMD:R_0603_1608Metric_Pad0.98x0.95mm_HandSolder |  |  |  | 0.139 |  | 3.0 | 0.417 | 5KOhm | ~ |  |  |  | https://www.digikey.co.th/en/products/detail/yageo/RT0603BRE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
R21 | Resistor_SMD:R_0603_1608Metric_Pad0.98x0.95mm_HandSolder |  |  |  | 0.009 |  | 1.0 | 0.009 | 1MOhm | ~ |  |  |  | https://www.digikey.co.th/en/products/detail/yageo/RC0603FR-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
R22,R24,R25,R26,R27,R28,R35,R36 | Resistor_SMD:R_0603_1608Metric_Pad0.98x0.95mm_HandSolder |  |  |  | 0.009 |  | 8.0 | 0.072 | 4.7KOhm | ~ |  |  |  | https://www.digikey.co.th/en/products/detail/yageo/RC0603FR-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
R23 | Resistor_SMD:R_0603_1608Metric_Pad0.98x0.95mm_HandSolder |  |  |  | 0.009 |  | 1.0 | 0.009 | 9.53KOhm | ~ |  |  |  | https://www.digikey.co.th/en/products/detail/yageo/RC0603FR-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
R31,R32 | Resistor_SMD:R_0603_1608Metric_Pad0.98x0.95mm_HandSolder |  |  |  | 0.02 |  | 2.0 | 0.04 | 25.5KOhm | ~ |  |  |  | https://www.digikey.co.th/en/products/detail/stackpole-elect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
U1 | SOIC_208MIL_WIN |  |  |  | 1.36 |  | 1.0 | 1.36 | W25Q128JVSIQ TR | W25Q128JVSIQ TR |  |  |  | https://www.mouser.com/ProductDetail/Winbond/W25Q128JVSIQ-TR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
U2,U3 | DRL0006A-MFG |  |  |  | 0.151 |  | 2.0 | 0.302 | TPS562243DRLR | TPS562243DRLR |  |  |  | https://www.digikey.co.th/en/products/detail/texas-instrumen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
U4 | TUSB8041RGCR:QFN50P900X900X100-65N |  |  |  | 2.6719 |  | 1.0 | 2.6719 | TUSB8041RGCR |  |  |  |  | https://th.mouser.com/ProductDetail/Texas-Instruments/TUSB80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
U5 | RTL8153B-VB-CG:QFN40P500X500X90-41N |  |  |  | 2.6908 |  | 1.0 | 2.6908 | RTL8153B-VB-CG |  |  |  |  | https://www.lcsc.com/product-detail/Ethernet-Transceivers_Re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
U13 | SC0914_13_:QFN40P700X700X90-57N |  |  |  | 0.7 |  | 1.0 | 0.7 | MCU_RaspberryPi_RP2040_RP2040 |  |  |  |  | https://www.digikey.co.th/en/products/detail/raspberry-pi/SC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
U7 | DBT0030A_N |  |  |  | 2.65 |  | 1.0 | 2.65 | PCM1860DBTR | PCM1860DBTR |  |  |  | https://www.mouser.com/ProductDetail/Texas-Instruments/PCM18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

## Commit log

2025-05-01 init repository
